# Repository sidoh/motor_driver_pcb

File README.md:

# Stepper Motor Driver PCB
Simple PCB for Wemos D1 Mini ESP8266 and an A4988 stepper driver

## Preview

## Ordering

You can order this board from OSH Park using [this link](https://oshpark.com/shared_projects/HcYJ5SwK).

The [gerber files archive](./gerbers/blinds_motor_driver.zip) can be used with other board houses (e.g., jlcpcb).

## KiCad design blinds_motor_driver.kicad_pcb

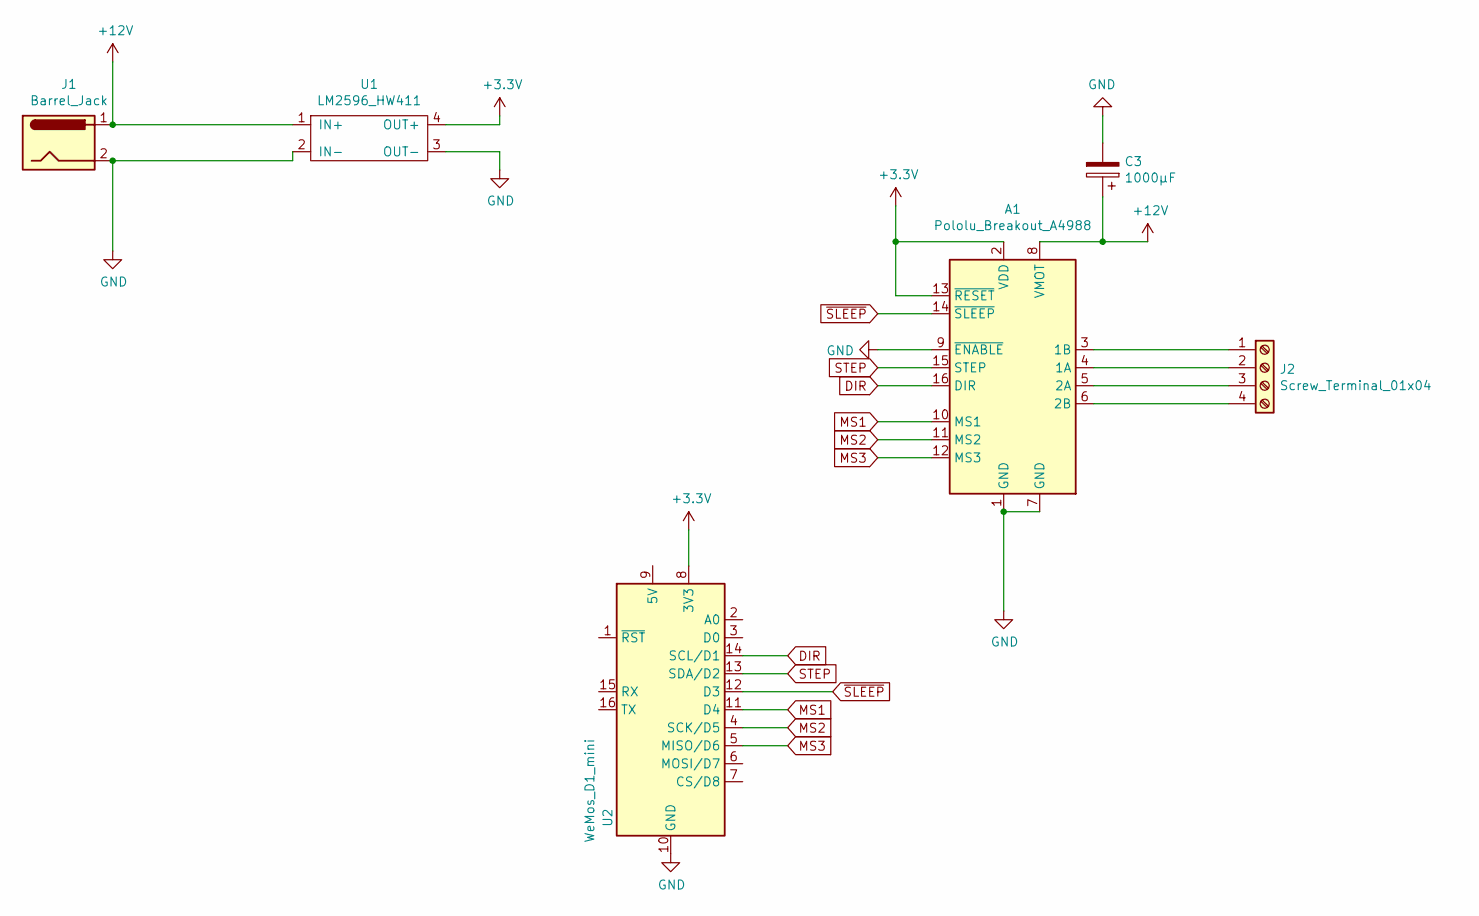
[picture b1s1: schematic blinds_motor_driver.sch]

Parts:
A1: Pololu_Breakout_A4988; Pololu_Breakout-16_15.2x20.3mm
C3: 1000µF; CP_Radial_D12.5mm_P5.00mm
J1: Barrel_Jack; Barrel_Jack_5.5mmODx2.1mmID_PJ-202A
J2: Screw_Terminal_01x04; TerminalBlock_bornier-4_P5.08mm
U1: LM2596_HW411
U2: WeMos_D1_mini; WEMOS_D1_mini_light

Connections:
+3V3: A1.2 (VDD), A1.13 (~RESET), U1.4 (OUT+), U2.8 (3V3)
+12V: A1.8 (VMOT), C3.1, J1.1, U1.1 (IN+)
DIR: A1.16 (DIR), U2.14 (SCL/D1)
GND: A1.1 (GND), A1.7 (GND), A1.9 (~ENABLE), C3.2, J1.2, U1.2 (IN-), U1.3 (OUT-), U2.10 (GND)
MS1: A1.10 (MS1), U2.11 (D4)
MS2: A1.11 (MS2), U2.4 (SCK/D5)
MS3: A1.12 (MS3), U2.5 (MISO/D6)
unnamed: A1.3 (1B), J2.1
unnamed: A1.4 (1A), J2.2
unnamed: A1.5 (2A), J2.3
unnamed: A1.6 (2B), J2.4
STEP: A1.15 (STEP), U2.13 (SDA/D2)
~SLEEP: A1.14 (~SLEEP), U2.12 (D3)

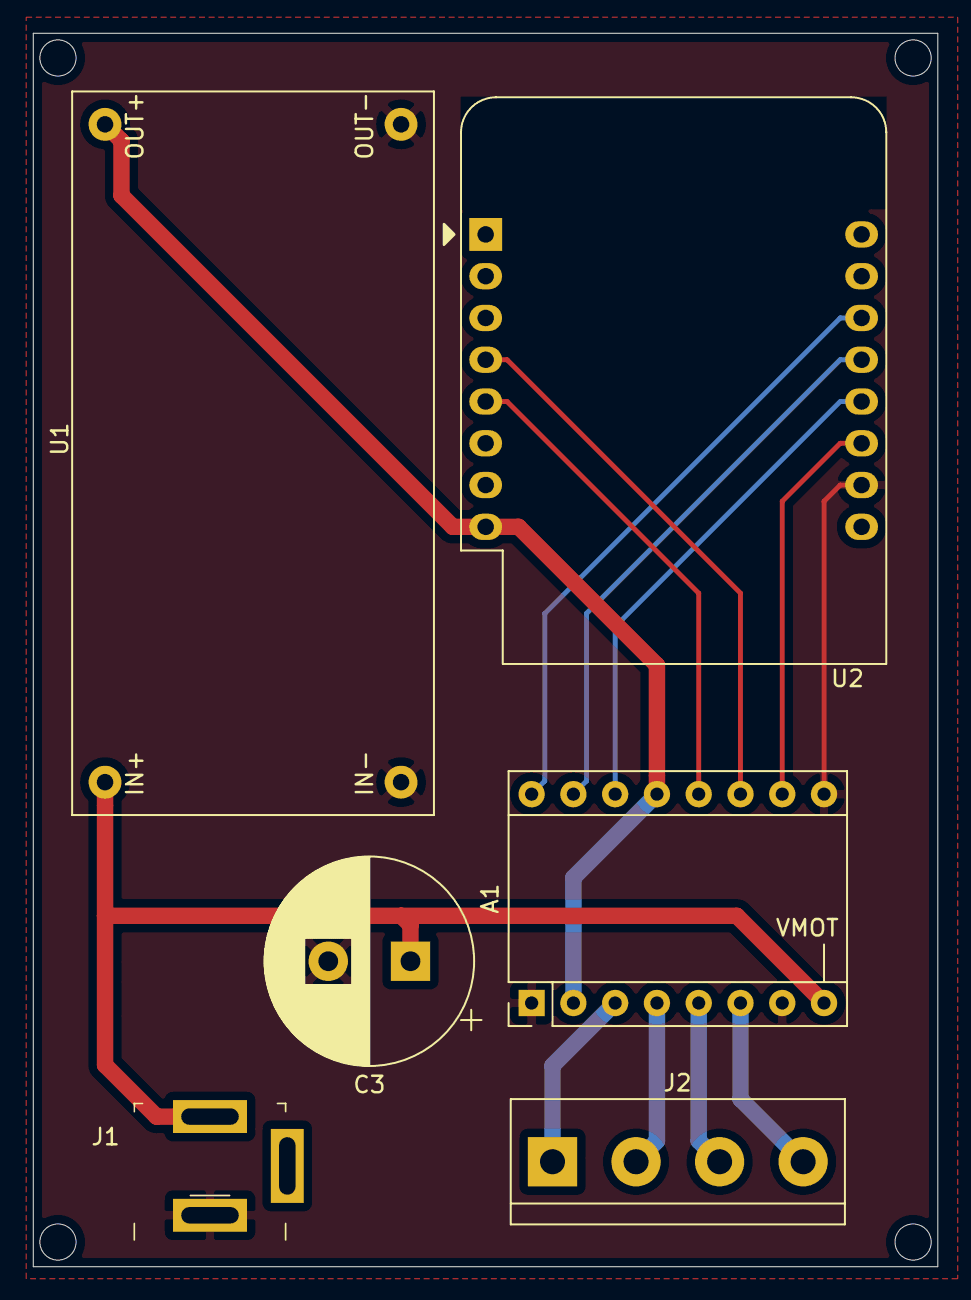
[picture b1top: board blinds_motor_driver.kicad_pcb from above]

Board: 2 copper layers, 55.0 x 75.0 mm, 6 parts (0 on the bottom side), 13 nets.

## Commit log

2020-02-17 Box schematic
2023-09-30 Add project box
